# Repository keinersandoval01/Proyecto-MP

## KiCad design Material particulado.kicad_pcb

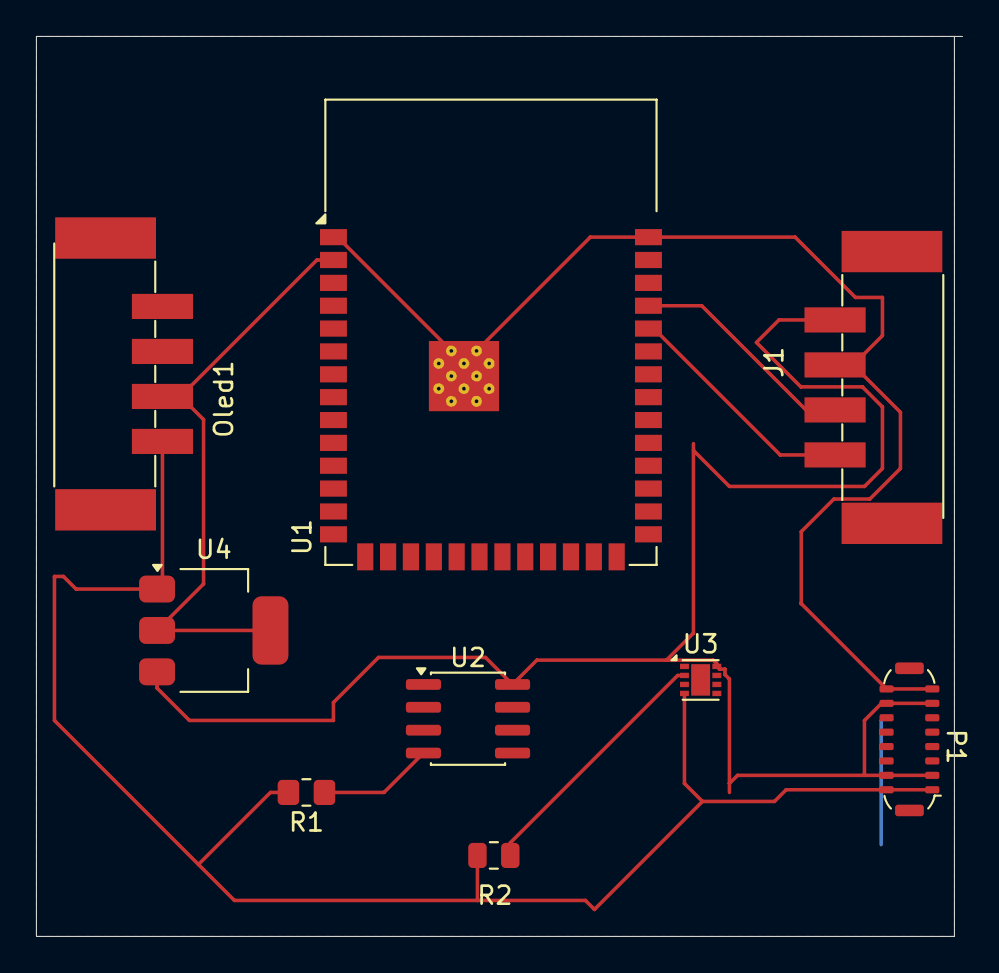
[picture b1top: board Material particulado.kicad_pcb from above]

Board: 2 copper layers, 51.5 x 50.0 mm, 9 parts (0 on the bottom side), 6 nets.

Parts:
J1: PMS; TerminalBlock_Phoenix_PTSM-0,5-4-2,5-V-SMD_1x04-1MP_P2.50mm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
Oled1: TerminalBlock_Phoenix_PTSM-0,5-4-2,5-V-SMD_1x04-1MP_P2.50mm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
P1: USB_C_Plug_USB2.0; USB_C_Plug_ShenzhenJingTuoJin_918-118A2021Y40002_Vertical
R1: 15k; R_0805_2012Metric_Pad1.20x1.40mm_HandSolder
R2: 2.2k; R_0805_2012Metric
U1: ESP32-S3-WROOM-1
U2: LM35-D; SOIC-8_3.9x4.9mm_P1.27mm
U3: LM358_DFN; DFN-8-1EP_2x2mm_P0.5mm_EP1.05x1.75mm
U4: Regulador de 5v a 3.3v; SOT-223-3_TabPin2

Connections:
+3V3: Oled1.2 (VCC), U1.2 (3V3), U4.2 (VO)
+5V: J1.1, P1.A4 (VBUS), P1.A9 (VBUS), P1.B4 (VBUS), P1.B9 (VBUS), U2.8 (+V_{S}), U3.8 (V+), U4.3 (VI)
GND: J1.2, Oled1.1 (GND), P1.A1 (GND), P1.A12 (GND), P1.B1 (GND), P1.B12 (GND), R1.2, R2.2, U1.1 (GND), U1.40 (GND), U1.41 (GND), U3.4 (V-), U4.1 (GND)
unnamed: R1.1, U2.4 (GND)
unnamed: R2.1, U3.2 (-)
RX(D0): J1.4, U1.36 (RXD0)

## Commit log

2026-05-15 Proyecto kicad iniciado
2026-05-15 cambie una resistencia
2026-05-15 parte analogica Keiner
2026-05-15 Huella y simbolo Oled Yara Camila
2026-05-15 Editando Huellas
2026-05-15 Organizando Huellas y smd -yara
2026-05-17 Corte cables
2026-05-21 Puse etiquetas y corte cables
2026-05-21 agregue el usb, un regulador de 5v a 3.3v y el bloque pms
2026-05-22 Hice cambios en las huellas
2026-05-23 cambie pistas-yara
